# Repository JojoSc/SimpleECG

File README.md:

# SimpleECG

This is a USB powered electrocardiograph, which streams the data straight to a computer. Currently it's a barebones version with just some basic protection.

It's a showcase of how easy it is to build your own "medical grade" ECG for ~50$ and should serve you as a starting point if you want to design and build your own. Also, I just really wanted to have an ECG...

**Some key data points:**

- ADS1298 analog frontend
- STM32F103 microprocessor
- USB power and data
- basic filtering and protection between patient and device, but no galvanic isolation between USB power source and PCB
- currently up to 2000 samples per second (limited by SPI speed, can be improved)

## Example Data

## Disclaimer
Don't actually use this in a clinical setting, it is a hobby project and lacks a lot of mandatory safety features for medical devices. For safety reasons I advise only connecting it to a battery powered laptop, which is not connected to an outlet.

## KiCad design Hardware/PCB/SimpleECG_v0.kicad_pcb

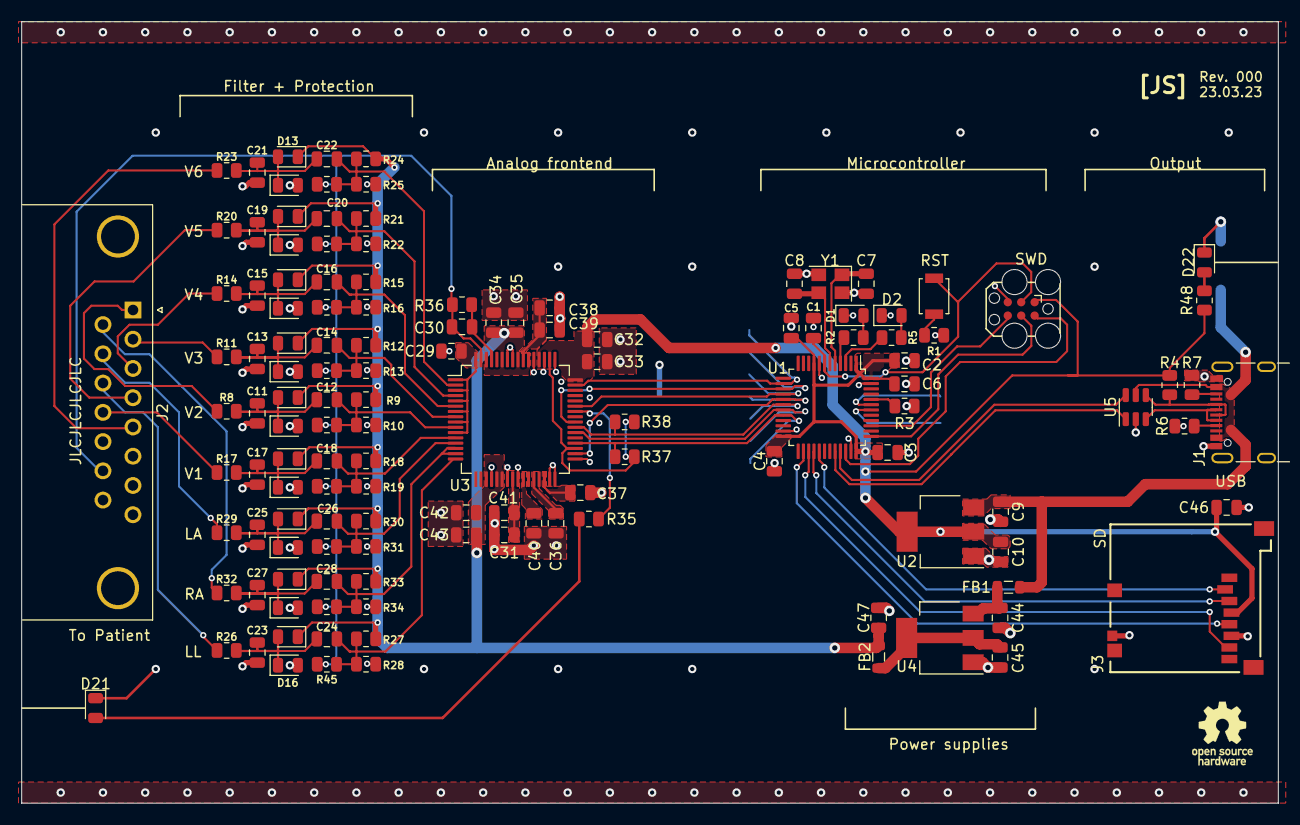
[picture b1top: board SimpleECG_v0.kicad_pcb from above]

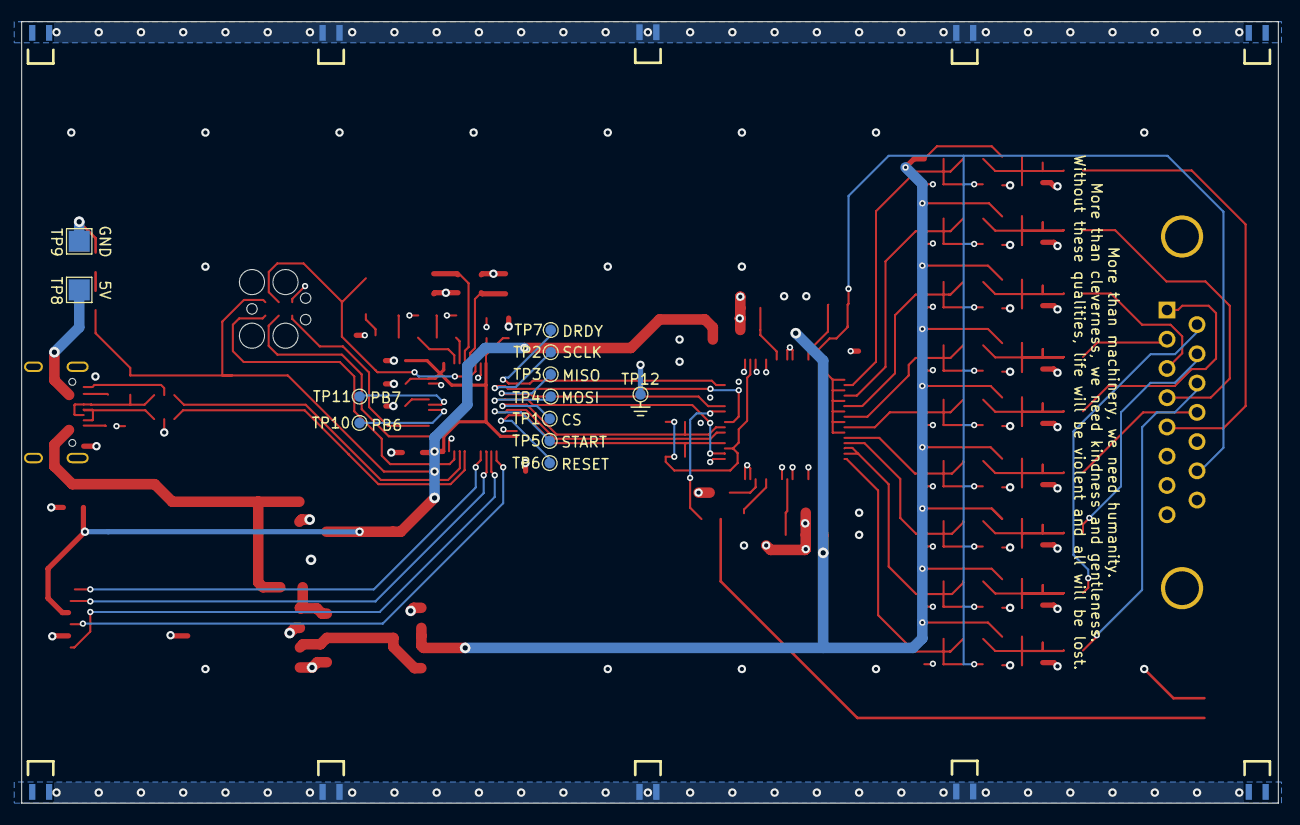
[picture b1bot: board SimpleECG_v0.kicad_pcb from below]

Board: 4 copper layers, 119.0 x 74.0 mm, 152 parts (22 on the bottom side), 75 nets.

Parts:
C1, C2, C3, C4, C5: 100nF; C_0805_2012Metric
C6: 10uF; C_0805_2012Metric
C7, C8, C11, C12, C13, C14, C15, C16, C17, C18, C19, C20, C21, C22, C23, C24, C25, C26, C27, C28, C29: C; C_0805_2012Metric
C9, C10, C44: 4u7; C_0805_2012Metric
C30: 1.5n; C_0805_2012Metric
C31, C45: 10u; C_0805_2012Metric
C32, C34, C39, C41, C43, C46, C47: 100n; C_0805_2012Metric
C33, C35, C37, C38, C40, C42: 1u; C_0805_2012Metric
C36: 22u; C_0805_2012Metric
D1, D2, D21, D22: LED; LED_0805_2012Metric
D3, D4, D5, D6, D7, D8, D9, D10, D11, D12, D13, D14, D15, D16, D17, D18, D19, D20: D; D_0805_2012Metric
FB1, FB2: FerriteBead; L_0805_2012Metric
J1: USB_C_Receptacle_USB2.0; USB_C_Receptacle_GCT_USB4105-xx-A_16P_TopMnt_Horizontal
J2: Conn_01x15; DSUB-15_Male_Horizontal_P2.77x2.84mm_EdgePinOffset7.70mm_Ho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
J3: Micro_SD_Card; GCT_MEM2051-00-195-00-A
R1, R35, R48: 1k; R_0805_2012Metric
R2, R5: 3.3k; R_0805_2012Metric
R3, R8, R11, R14, R17, R20, R23, R26, R29, R32, R37, R38: 10k; R_0805_2012Metric
R4: 1.5k; R_0805_2012Metric
R6, R7: 5k1; R_0805_2012Metric
R9, R10, R12, R13, R15, R16, R18, R19, R21, R22, R24, R25, R27, R28, R30, R31, R33, R34, R39, R40, R41, R42, R43, R44, R45, R46, R47: R; R_0805_2012Metric
R36: 1M; R_0805_2012Metric
SHLD4, SHLD4#2, SHLD4#3, SHLD4#4, SHLD4#5, SHLD4#6, SHLD4#7, SHLD4#8, SHLD4#9, SHLD4#10: SHLD_FINGER_0820; EMI_SHLD_FINGER_0820
SW1: SW_Push; SW_SPST_B3U-1100P
TC1: TC2030-IDC; Tag-Connect_TC2030-IDC-FP_2x03_P1.27mm_Vertical
TP1, TP2, TP3, TP4, TP5, TP6, TP7: TestPoint_Small; TestPoint_Pad_D1.0mm
TP8, TP9: TestPoint; TestPoint_Pad_2.0x2.0mm
TP10, TP11, TP12: TestPoint; TestPoint_Pad_D1.0mm
U1: STM32F103CBTx; LQFP-48_7x7mm_P0.5mm
U2, U4: AMS1117-3.3; SOT-223-3_TabPin2
U3: ADS1298xPAG; TQFP-64_10x10mm_P0.5mm
U5: SOT-23-6
Y1: 8 MHz; Crystal_SMD_3225-4Pin_3.2x2.5mm

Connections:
+3.3VADC: C34.1, C35.1, C42.1, C43.1, C47.1, D3.1 (K), D5.1 (K), D7.1 (K), D9.1 (K), D11.1 (K), D13.1 (K), D15.1 (K), D17.1 (K), D19.1 (K), FB2.2, R9.1, R12.1, R15.1, R18.1, R21.1, R24.1, R27.1, R30.1, R33.1, U3.19 (AVDD), U3.21 (AVDD), U3.22 (AVDD), U3.54 (AVDD1), U3.56 (AVDD), U3.59 (AVDD), U3.62 (RLDIN)
+3V3: C2.1, C3.1, C4.1, C5.1, C6.1, C10.1, C32.1, C33.1, C46.1, J3.4 (VDD), R4.2, R37.1, R38.1, R48.1, TC1.1 (VCC), U1.1 (VBAT), U1.9 (VDDA), U1.24 (VDD), U1.36 (VDD), U1.48 (VDD), U2.2 (VO), U3.35 (~PWDN), U3.48 (DVDD), U3.50 (DVDD), U3.52 (CLKSEL)
/AFE/ADS_STATUS: R35.1, U3.42 (GPIO1)
/AFE/LA: J2.10, R29.1
/AFE/LA_filtered: C26.2, R30.2, R31.1, R46.2, U3.13 (IN2N)
/AFE/LL: J2.11, R26.1
/AFE/LL_filtered: C24.2, R27.2, R28.1, R45.2, U3.16 (IN1P)
/AFE/MISO: TP3.1, U1.16 (PA6), U3.43 (DOUT)
/AFE/MOSI: TP4.1, U1.17 (PA7), U3.34 (DIN)
/AFE/RA: J2.9, R32.1
/AFE/RA_filtered: C28.2, R33.2, R34.1, R47.2, U3.14 (IN2P), U3.15 (IN1N)
/AFE/SCLK: TP2.1, U1.15 (PA5), U3.40 (SCLK)
/AFE/START: TP5.1, U1.19 (PB1), U3.38 (START)
/AFE/V1: J2.12, R17.1
/AFE/V1_filtered: C18.2, R18.2, R19.1, R42.2, U3.12 (IN3P)
/AFE/V2: J2.1, R8.1
/AFE/V2_filtered: C12.2, R9.2, R10.1, R39.2, U3.10 (IN4P)
/AFE/V3: J2.2, R11.1
/AFE/V3_filtered: C14.2, R12.2, R13.1, R40.2, U3.8 (IN5P)
/AFE/V4: J2.3, R14.1
/AFE/V4_filtered: C16.2, R15.2, R16.1, R41.2, U3.6 (IN6P)
/AFE/V5: J2.4, R20.1
/AFE/V5_filtered: C20.2, R21.2, R22.1, R43.2, U3.4 (IN7N)
/AFE/V6: J2.5, R23.1
/AFE/V6_filtered: C22.2, R24.2, R25.1, R44.2, U3.2 (IN8P)
/AFE/VCAP1: C36.1, U3.28 (VCAP1)
/AFE/VCAP2: C37.1, U3.30 (VCAP2)
/AFE/VCAP3: C38.1, C39.1, U3.55 (VCAP3)
/AFE/VCAP4: C40.1, U3.26 (VCAP4)
/AFE/VREFP: C31.1, C41.1, U3.24 (VREFP)
/AFE/WCT: C29.1, U3.1 (IN8N), U3.3 (IN7P), U3.5 (IN6N), U3.7 (IN5N), U3.9 (IN4N), U3.11 (IN3N), U3.64 (WCT)
/AFE/~CS: R38.2, TP1.1, U1.18 (PB0), U3.39 (~CS)
/AFE/~DRDY: TP7.1, U1.14 (PA4), U3.47 (~DRDY)
/AFE/~RESET: R37.2, TP6.1, U1.20 (PB2), U3.36 (~RESET)
/Power/CC1: J1.A5 (CC1), R6.1
/Power/CC2: J1.B5 (CC2), R7.2
/Power/U_USB_D+: J1.A6 (D+), J1.B6 (D+), R4.1, U5.4 (B_{In})
/Power/U_USB_D-: J1.A7 (D-), J1.B7 (D-), U5.3 (A_{In})
/Power/VBUS: C9.1, FB1.1, J1.A4 (VBUS), J1.A9 (VBUS), J1.B4 (VBUS), J1.B9 (VBUS), TP8.1, U2.3 (VI), U5.5 (V+)
/SD_CS: J3.2 (DAT3/CD), U1.29 (PA8)
/SPI2_CLK: J3.5 (CLK), U1.26 (PB13)
/SPI2_MISO: J3.7 (DAT0), U1.27 (PB14)
/SPI2_MOSI: J3.3 (CMD), U1.28 (PB15)
/STM32F1/BOOT0: R3.2, U1.44 (BOOT0)
/STM32F1/ERROR_LED: R5.1, U1.3 (PC14)
/STM32F1/NRST: C1.1, SW1.2, TC1.3 (NRESET), U1.7 (NRST)
/STM32F1/OSC_IN: C7.1, U1.5 (PD0), Y1.1
/STM32F1/OSC_OUT: C8.1, U1.6 (PD1), Y1.3
/STM32F1/PB6: TP10.1, U1.42 (PB6)
/STM32F1/PB7: TP11.1, U1.43 (PB7)
/STM32F1/STATUS_LED: R2.1, U1.4 (PC15)
/STM32F1/SWCLK: TC1.4 (SWCLK), U1.37 (PA14)
/STM32F1/SWDIO: TC1.2 (SWDIO), U1.34 (PA13)
/STM32F1/SWSWO: TC1.6 (SWO), U1.39 (PB3)
GND: C1.2, C2.2, C3.2, C4.2, C5.2, C6.2, C7.2, C8.2, C9.2, C10.2, C11.2, C13.2, C15.2, C17.2, C19.2, C21.2, C23.2, C25.2, C27.2, C29.2, C31.2, C32.2, C33.2, C34.2, C35.2, C36.2, C37.2, C38.2, C39.2, C40.2, C41.2, C42.2, C43.2, C44.2, C45.2, C46.2, C47.2, D1.1 (K), D2.1 (K), D4.2 (A), D6.2 (A), D8.2 (A), D10.2 (A), D12.2 (A), D14.2 (A), D16.2 (A), D18.2 (A), D20.2 (A), D21.1 (K), D22.1 (K), J1.A1 (GND), J1.A12 (GND), J1.B1 (GND), J1.B12 (GND), J2.6, J3.6 (VSS), J3.9 (SHIELD), R1.1, R3.1, R6.2, R7.1, R10.2, R13.2, R16.2, R19.2, R22.2, R25.2, R28.2, R31.2, R34.2, SHLD4.1, SHLD4#2.1, SHLD4#3.1, SHLD4#4.1, SHLD4#5.1, SHLD4#8.1, TC1.5 (GND), TP9.1, TP12.1, U1.8 (VSSA), U1.23 (VSS), U1.35 (VSS), U1.47 (VSS), U2.1 (GND), U3.20 (AVSS), U3.23 (AVSS), U3.25 (VREFN), U3.31 (RESV1), U3.32 (AVSS), U3.33 (DGND), U3.49 (DGND), U3.51 (DGND), U3.53 (AVSS1), U3.57 (AVSS), U3.58 (AVSS), U4.1 (GND), U5.2 (V-), Y1.2, Y1.4
unnamed: D1.2 (A), R2.2
unnamed: D2.2 (A), R5.2
unnamed: C11.1, C12.1, D3.2 (A), D4.1 (K), R8.2
unnamed: C13.1, C14.1, D5.2 (A), D6.1 (K), R11.2
unnamed: C15.1, C16.1, D7.2 (A), D8.1 (K), R14.2
unnamed: C17.1, C18.1, D9.2 (A), D10.1 (K), R17.2
unnamed: C19.1, C20.1, D11.2 (A), D12.1 (K), R20.2
unnamed: C21.1, C22.1, D13.2 (A), D14.1 (K), R23.2
unnamed: C23.1, C24.1, D15.2 (A), D16.1 (K), R26.2
unnamed: C25.1, C26.1, D17.2 (A), D18.1 (K), R29.2
unnamed: C27.1, C28.1, D19.2 (A), D20.1 (K), R32.2
unnamed: D21.2 (A), R35.2
unnamed: D22.2 (A), R48.2
unnamed: R1.2, SW1.1
unnamed: C30.2, R36.2, U3.61 (RLDINV)
unnamed: C44.1, FB1.2, U4.3 (VI)
unnamed: C45.1, FB2.1, U4.2 (VO)
RL: C30.1, J2.14, R36.1, R39.1, R40.1, R41.1, R42.1, R43.1, R44.1, R45.1, R46.1, R47.1, U3.63 (RLDOUT)
USB_D+: U1.33 (PA12), U5.6 (B_{Out})
USB_D-: U1.32 (PA11), U5.1 (A_{OUT})

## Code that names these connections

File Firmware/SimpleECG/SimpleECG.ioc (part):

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Mcu.Name=STM32F103C(8-B)Tx
Mcu.Package=LQFP48
Mcu.UserName=STM32F103CBTx
PA11.Mode=Device
PA11.Signal=USB_DM
PA12.Mode=Device
PA12.Signal=USB_DP
PA13.Mode=Serial_Wire
PA13.Signal=SYS_JTMS-SWDIO
PA14.Mode=Serial_Wire
PA14.Signal=SYS_JTCK-SWCLK
PA4.GPIOParameters=GPIO_Label
PA4.GPIO_Label=nDRDY
PA4.Signal=GPIO_Input
PA5.Mode=Full_Duplex_Master
PA5.Signal=SPI1_SCK
PA6.Mode=Full_Duplex_Master
PA6.Signal=SPI1_MISO
PA7.Mode=Full_Duplex_Master
PA7.Signal=SPI1_MOSI
PB0.GPIOParameters=GPIO_Label
PB0.GPIO_Label=nCS
PB0.Signal=GPIO_Output
PB1.GPIOParameters=GPIO_Label
PB1.GPIO_Label=START
PB1.Signal=GPIO_Output
PB2.GPIOParameters=GPIO_Label
PB2.GPIO_Label=nRESET
PB2.Signal=GPIO_Output
PC14-OSC32_IN.GPIOParameters=GPIO_Label
PC14-OSC32_IN.GPIO_Label=LED_ERROR
PC14-OSC32_IN.Signal=GPIO_Output
PC15-OSC32_OUT.GPIOParameters=GPIO_Label
PC15-OSC32_OUT.GPIO_Label=LED_STATUS
PC15-OSC32_OUT.Signal=GPIO_Output
PD0-OSC_IN.Mode=HSE-External-Oscillator
PD0-OSC_IN.Signal=RCC_OSC_IN
PD1-OSC_OUT.Mode=HSE-External-Oscillator
PD1-OSC_OUT.Signal=RCC_OSC_OUT
RCC.SYSCLKFreq_VALUE=48000000
RCC.SYSCLKSource=RCC_SYSCLKSOURCE_PLLCLK
board=custom

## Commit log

2023-04-25 Init
2023-04-25 Added license
2024-02-02 First working version, with 12-lead recording
2024-02-02 Added sample image
